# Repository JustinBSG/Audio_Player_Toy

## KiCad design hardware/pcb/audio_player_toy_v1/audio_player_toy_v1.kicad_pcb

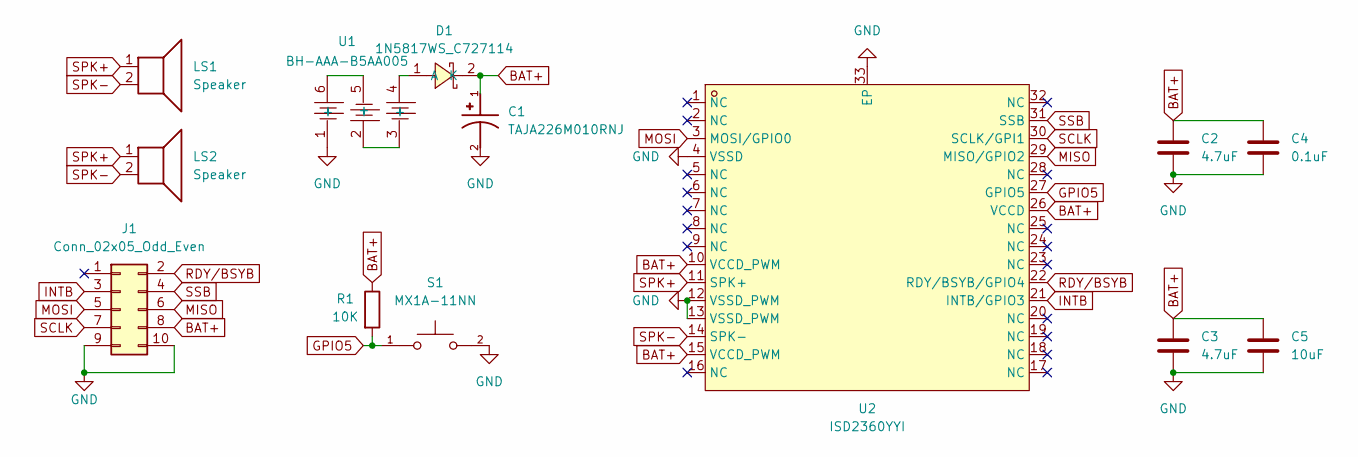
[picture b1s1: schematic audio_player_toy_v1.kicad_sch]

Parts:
C1: TAJA226M010RNJ; CAPMP3216X180N; PARTREV 031320
C2, C3: 4.7uF; C_0603_1608Metric
C4: 0.1uF; R_0603_1608Metric
C5: 10uF; R_0603_1608Metric
D1: 1N5817WS_C727114; SOD-323_L1.8-W1.3-LS2.5-FD; LCSC Part C727114
J1: Conn_02x05_Odd_Even; PinHeader_2x05_P2.54mm_Vertical
LS1: Speaker; Speaker_SMD
LS2: Speaker; Speaker_TH
R1: 10K; R_0603_1608Metric
S1: MX1A-11NN; SW_MX1A-11NN
U1: BH-AAA-B5AA005; BAT-SMD_BH-AAA-B5AA005; LCSC Part C2979170
U2: ISD2360YYI; TQFN-32_L5.0-W5.0-P0.50-BL-EP3.5; LCSC Part C4991039

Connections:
BAT+: C1.1, C2.1, C3.1, C4.1, C5.1, D1.2 (K), J1.8, R1.1, U2.10 (VCCD_PWM), U2.15 (VCCD_PWM), U2.26 (VCCD)
GND: C1.2, C2.2, C3.2, C4.2, C5.2, J1.9, J1.10, S1.2, U1.1 (-), U2.4 (VSSD), U2.12 (VSSD_PWM), U2.13 (VSSD_PWM), U2.33 (EP)
GPIO5: R1.2, S1.1, U2.27 (GPIO5)
INTB: J1.3, U2.21 (INTB/GPIO3)
MISO: J1.6, U2.29 (MISO/GPIO2)
MOSI: J1.5, U2.3 (MOSI/GPIO0)
unnamed: D1.1 (A), U1.4 (+)
unnamed: U1.2 (+), U1.3 (-)
unnamed: U1.5 (-), U1.6 (+)
RDY/BSYB: J1.2, U2.22 (RDY/BSYB/GPIO4)
SCLK: J1.7, U2.30 (SCLK/GPI1)
SPK+: LS1.1, LS2.1, U2.11 (SPK+)
SPK-: LS1.2, LS2.2, U2.14 (SPK-)
SSB: J1.4, U2.31 (SSB)

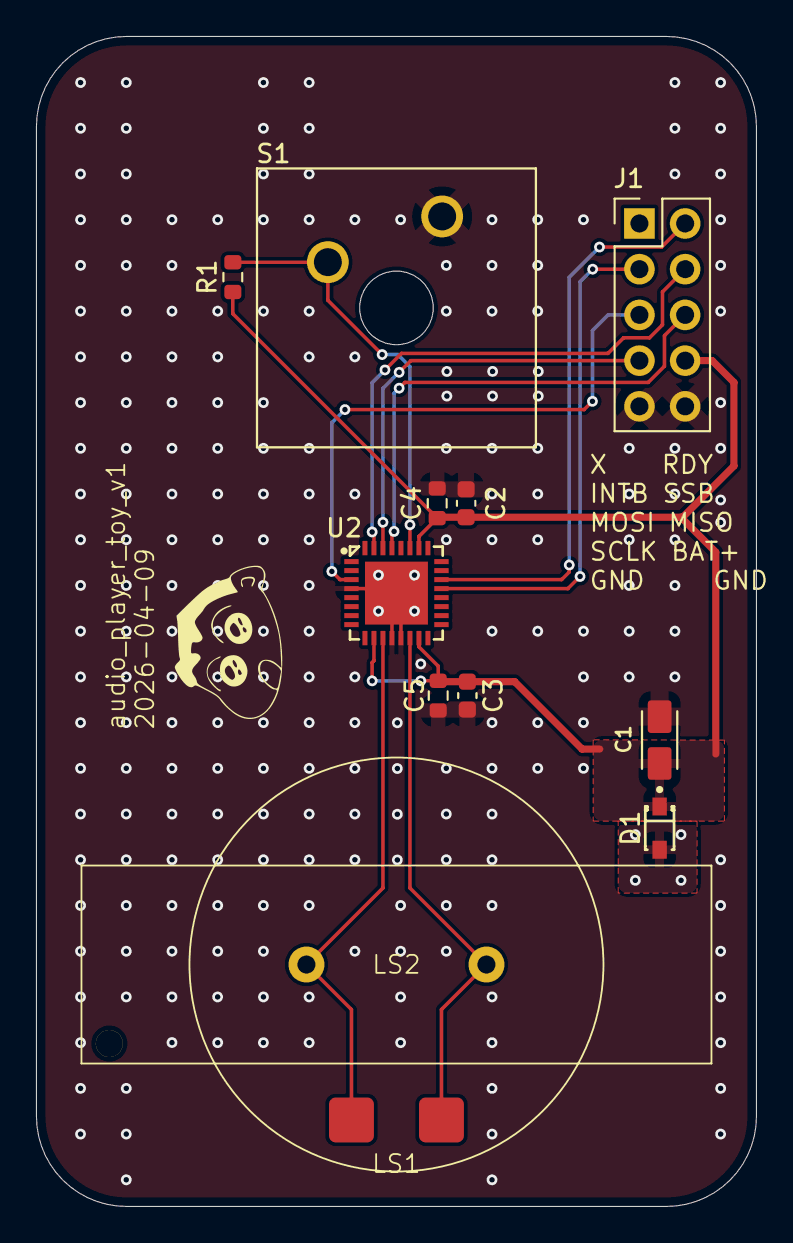
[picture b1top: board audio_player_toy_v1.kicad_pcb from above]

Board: 2 copper layers, 40.0 x 65.0 mm, 13 parts (1 on the bottom side), 14 nets.

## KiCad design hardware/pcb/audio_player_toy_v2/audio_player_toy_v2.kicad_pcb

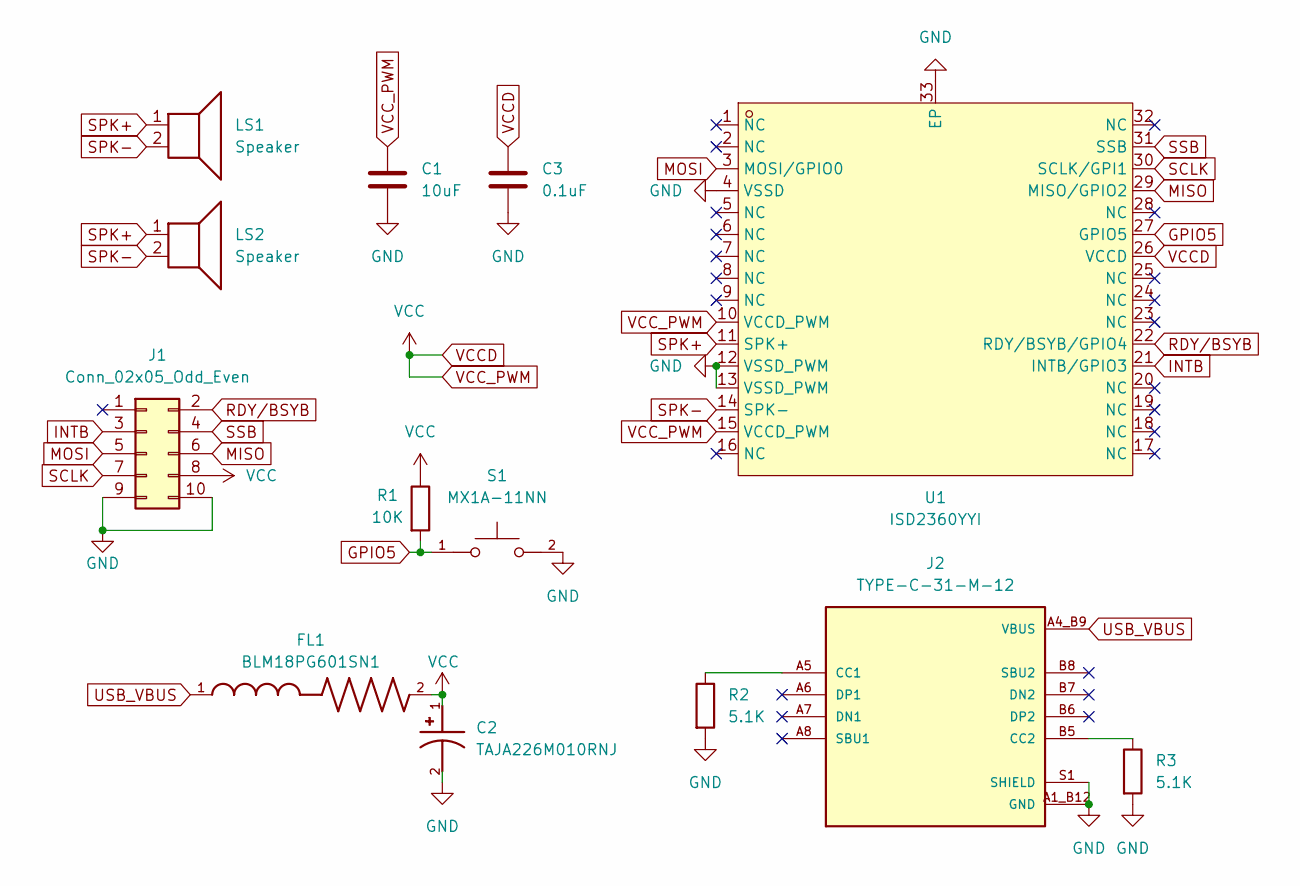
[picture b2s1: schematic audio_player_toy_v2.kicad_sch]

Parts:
C1: 10uF; R_0603_1608Metric
C2: TAJA226M010RNJ; CAPMP3216X180N; PARTREV 031320
C3: 0.1uF; R_0603_1608Metric
FL1: BLM18PG601SN1; BEADC1608X95N
J1: Conn_02x05_Odd_Even; PinHeader_2x05_P2.54mm_Vertical
J2: TYPE-C-31-M-12; HRO_TYPE-C-31-M-12; PARTREV 2020.12.08
LS1: Speaker; Speaker_SMD
LS2: Speaker; Speaker_TH
R1: 10K; R_0603_1608Metric
R2, R3: 5.1K; R_0603_1608Metric
S1: MX1A-11NN; SW_MX1A-11NN
U1: ISD2360YYI; TQFN-32_L5.0-W5.0-P0.50-BL-EP3.5; LCSC Part C4991039

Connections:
GND: C1.2, C2.2, C3.2, J1.9, J1.10, J2.A1_B12 (GND), J2.B1_A12 (GND), J2.S1 (SHIELD), J2.S2 (SHIELD), J2.S3 (SHIELD), J2.S4 (SHIELD), R2.2, R3.2, S1.2, U1.4 (VSSD), U1.12 (VSSD_PWM), U1.13 (VSSD_PWM), U1.33 (EP)
GPIO5: R1.2, S1.1, U1.27 (GPIO5)
INTB: J1.3, U1.21 (INTB/GPIO3)
MISO: J1.6, U1.29 (MISO/GPIO2)
MOSI: J1.5, U1.3 (MOSI/GPIO0)
unnamed: J2.A5 (CC1), R2.1
unnamed: J2.B5 (CC2), R3.1
RDY/BSYB: J1.2, U1.22 (RDY/BSYB/GPIO4)
SCLK: J1.7, U1.30 (SCLK/GPI1)
SPK+: LS1.1, LS2.1, U1.11 (SPK+)
SPK-: LS1.2, LS2.2, U1.14 (SPK-)
SSB: J1.4, U1.31 (SSB)
USB_VBUS: FL1.1, J2.A4_B9 (VBUS), J2.B4_A9 (VBUS)
VCCD: C1.1, C2.1, C3.1, FL1.2, J1.8, R1.1, U1.10 (VCCD_PWM), U1.15 (VCCD_PWM), U1.26 (VCCD)

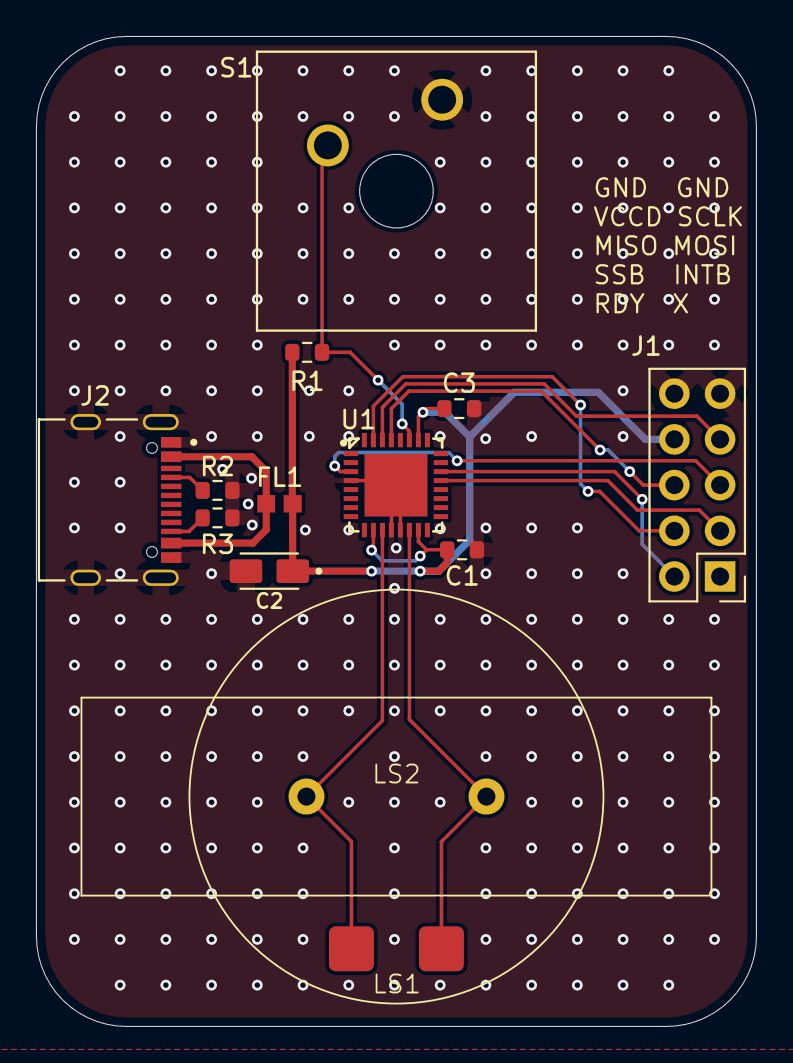
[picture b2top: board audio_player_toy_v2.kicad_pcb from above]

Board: 2 copper layers, 40.0 x 55.0 mm, 13 parts (0 on the bottom side), 14 nets.

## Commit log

2026-03-24 chore: reset project and use another hardware design
2026-03-31 doc: remove unneccessary component
2026-03-31 chore: add footprint of audio ic and aaa holder
2026-04-01 chore: add qfn footprint audio ic
2026-04-01 chore: add cherry mx footprint
2026-04-01 doc: add audio ic doc
2026-04-01 feat: complete sch of v1
2026-04-01 feat: add TH speaker capacbility
2026-04-01 chore: update footprint of speaker TH
2026-04-02 chore: finalize the location of main component
2026-04-02 chore: resize the pcb
2026-04-02 feat: finish routing pcb
2026-04-02 chore: create v2 for usb power supply
2026-04-02 feat: finish schematics of v2
2026-04-02 chore: change combination of decoupling caps in both versions
2026-04-02 chore: complete finding all footprints, ready to routing, both version
2026-04-04 feat: complete sch and pcb of v1
2026-04-08 chore: update decoupling caps in v1
2026-04-08 feat: finish routing v2
2026-04-08 chore: add dimension on v2
2026-04-08 chore: create combine board
2026-04-09 chore: remove combine prj
2026-04-09 fix: fix annotation
2026-04-09 chore: add label on v1 and v2
2026-04-09 doc: generate BOM for v1 and v2
2026-04-09 doc: generate production data of v1 and v2
2026-04-10 doc: generate all production data
